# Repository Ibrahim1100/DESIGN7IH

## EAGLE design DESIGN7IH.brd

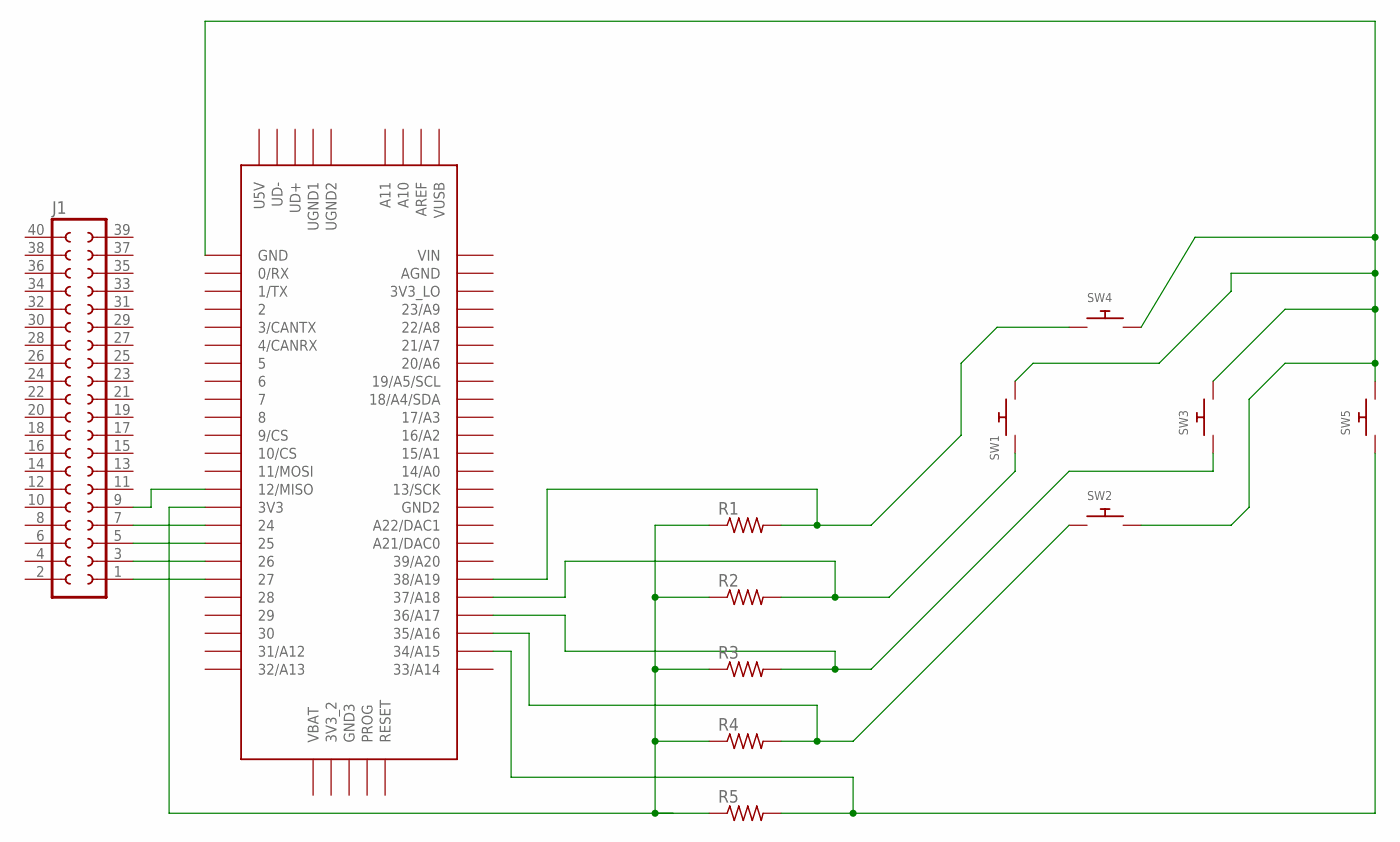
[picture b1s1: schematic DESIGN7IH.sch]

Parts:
J1: SOCKET-40V; S40V
R1, R2, R3, R4, R5: R-US_0204/5; 0204/5
SW1, SW2, SW3, SW4, SW5: SWITCH_PUSHBUTTONEVQ-PE; TACT_PANA-EVQ
U$1: TEENSY_3.5/3.6

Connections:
unnamed: R1.1, R2.1, R3.1, R4.1, R5.1, U$1.3V3
unnamed: R5.2, SW5.P$1, U$1.34/A15
unnamed: SW1.P$2, SW2.P$2, SW3.P$2, SW4.P$2, SW5.P$2, U$1.GND
unnamed: R3.2, SW3.P$1, U$1.36/A17
unnamed: R4.2, SW2.P$1, U$1.35/A16
unnamed: R2.2, SW1.P$1, U$1.37/A18
unnamed: R1.2, SW4.P$1, U$1.38/A19
unnamed: J1.1, U$1.27
unnamed: J1.3, U$1.26
unnamed: J1.5, U$1.25
unnamed: J1.7, U$1.24
unnamed: J1.9, U$1.12/MISO

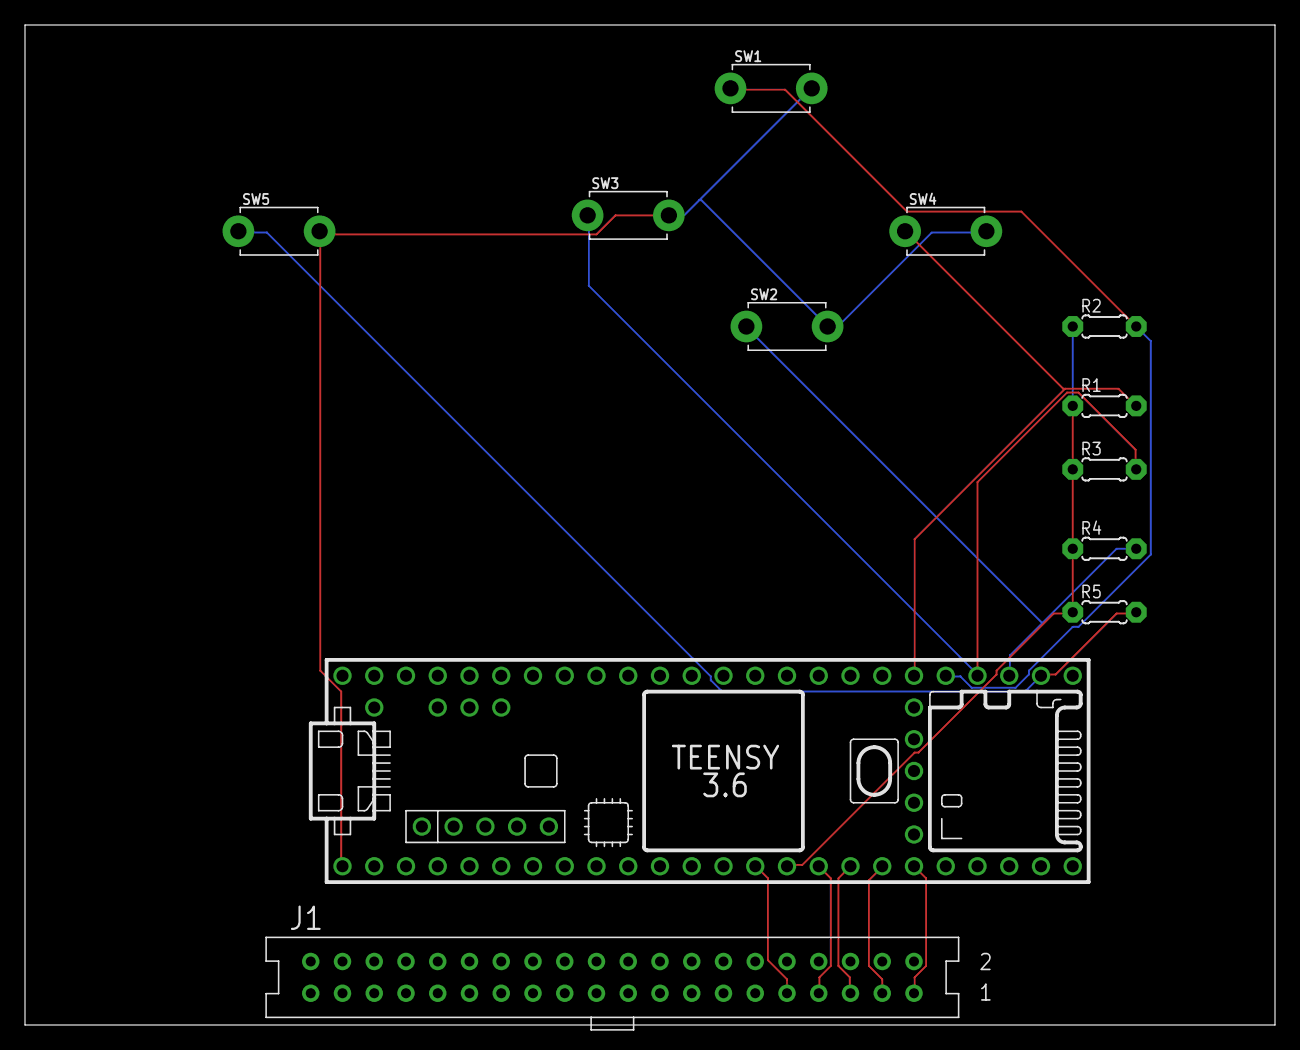
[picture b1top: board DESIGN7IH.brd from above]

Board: 2 copper layers, 100.0 x 80.0 mm, 12 parts (0 on the bottom side), 12 nets.
